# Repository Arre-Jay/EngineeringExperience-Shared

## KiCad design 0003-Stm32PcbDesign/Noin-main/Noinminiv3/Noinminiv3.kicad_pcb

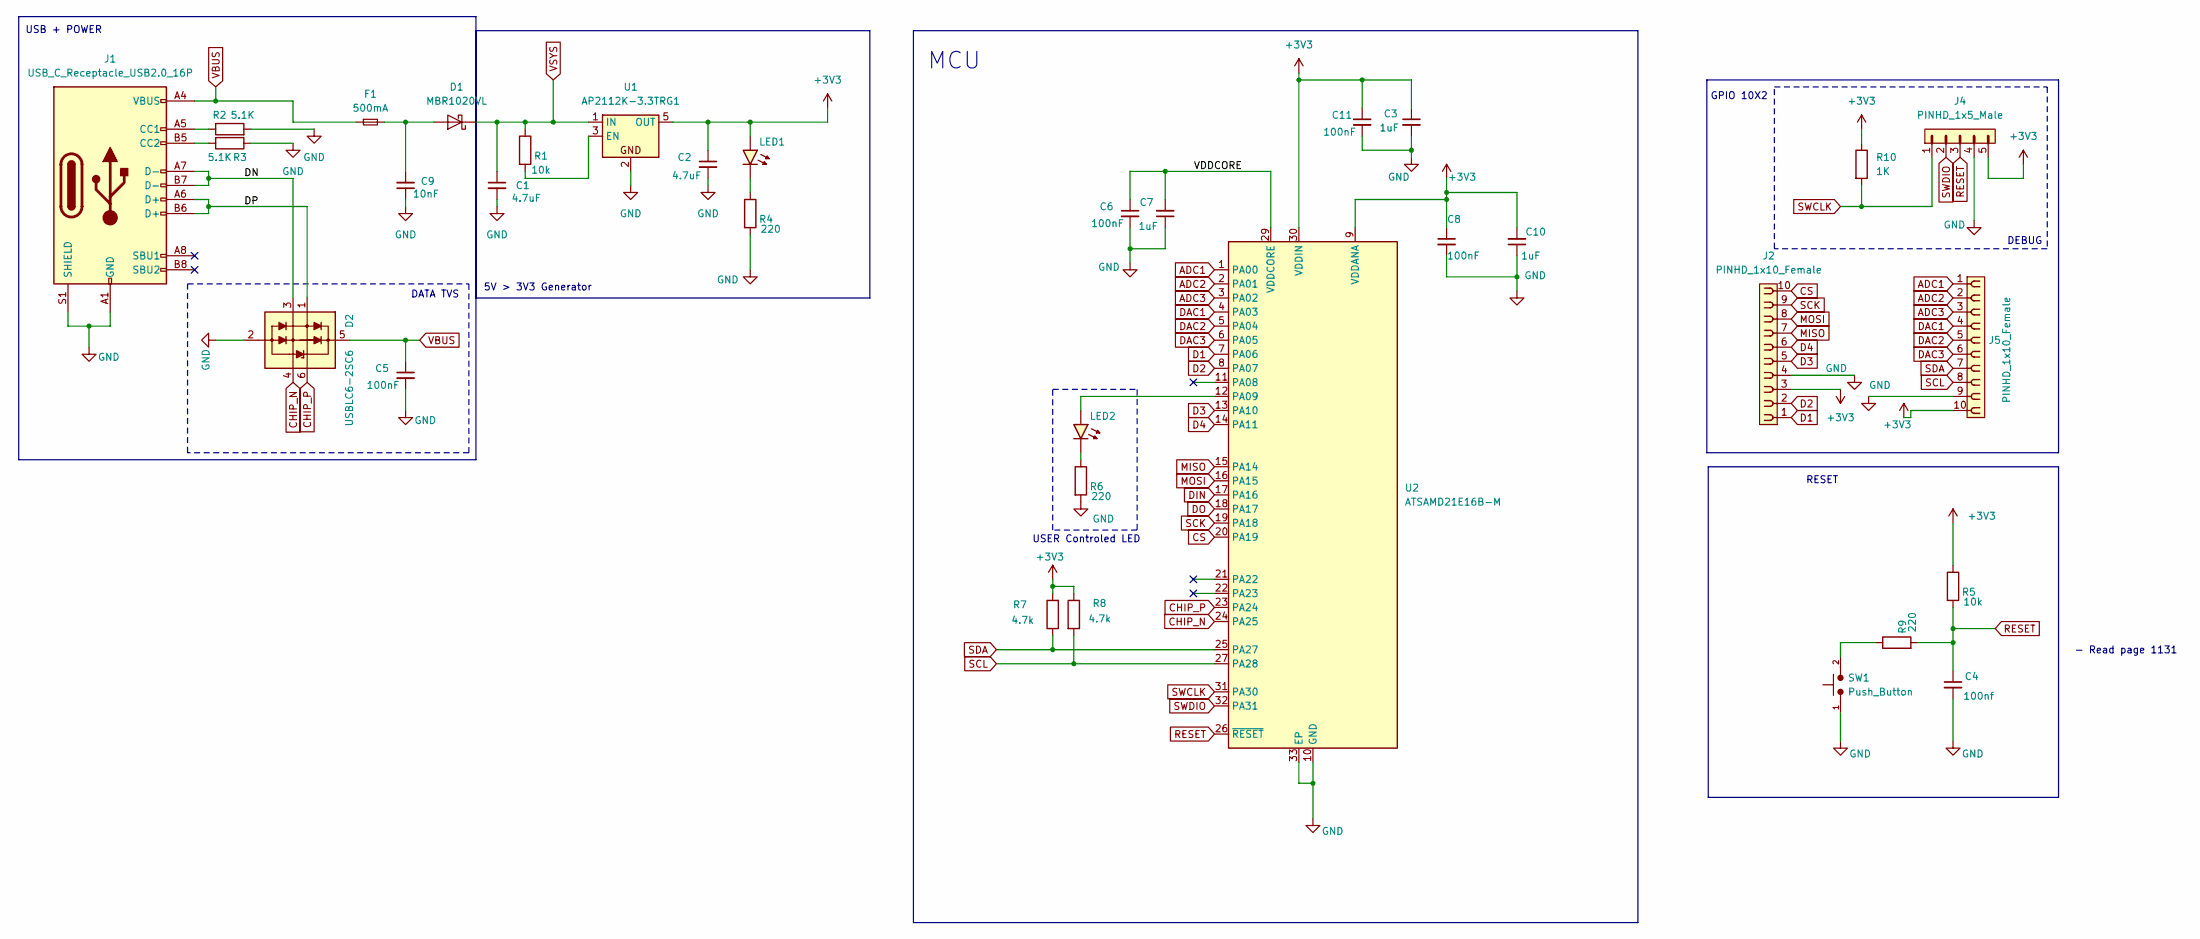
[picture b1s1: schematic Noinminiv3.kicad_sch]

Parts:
C1, C2, C3, C4, C5, C6, C7, C8, C9, C10, C11: 1uF_0603_25V; C_0603_1608Metric; Part Number GRM188R61E105KA12D; JLCPCB ID C15849
D1: MBR1020VL; D_SOD-123F_TVS
D2: USBLC6-2SC6; SOT-23-6
F1: 500mA; Fuse_0603_1608Metric
J1: USB_C_Receptacle_USB2.0_16P; USB_C_Receptacle_HRO_TYPE-C-31-M-12
J2, J5: PINHD_1x10_Female; PinSocket_1x10_P2.54mm_Vertical
J4: PINHD_1x5_Male; PinHeader_1x05_P2.54mm_Vertical
LED1, LED2: LED_1.8mm_SMD_Red; LED_0402_1005Metric
R1, R2, R3, R4, R5, R6, R7, R8, R9: 10k_0402; R_0402; Part Number RT0402FRE0710KL
R10: 1K; R_0402; Manufacturer Part Number 0402WGF1001TCE
SW1: Push_Button; SW_Push_SPST_NO_Alps_SKRK
U1: AP2112K-3.3TRG1; SOT-23-5
U2: ATSAMD21E16B-M; QFN-32-1EP_5x5mm_P0.5mm_EP3.6x3.6mm

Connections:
+3V3: C2.1, C3.1, C8.1, C10.2, C11.1, J2.3, J4.5, J5.10, LED1.2 (A), R5.1, R7.2, R8.1, R10.1, U1.5 (OUT), U2.9 (VDDANA), U2.30 (VDDIN)
/DN: D2.3 (L2), J1.A7 (D-), J1.B7 (D-)
/DP: D2.1 (L1), J1.A6 (D+), J1.B6 (D+)
/VDDCORE: C6.1, C7.2, U2.29 (VDDCORE)
ADC1: J5.1, U2.1 (PA00)
ADC2: J5.2, U2.2 (PA01)
ADC3: J5.3, U2.3 (PA02)
CHIP_N: D2.4 (L2), U2.24 (PA25)
CHIP_P: D2.6 (L1), U2.23 (PA24)
CS: J2.10, U2.20 (PA19)
D1: J2.1, U2.7 (PA06)
D2: J2.2, U2.8 (PA07)
D3: J2.5, U2.13 (PA10)
D4: J2.6, U2.14 (PA11)
DAC1: J5.4, U2.4 (PA03)
DAC2: J5.5, U2.5 (PA04)
DAC3: J5.6, U2.6 (PA05)
DIN: U2.17 (PA16)
DO: U2.18 (PA17)
GND: C1.2, C2.2, C3.2, C4.2, C5.2, C6.2, C7.1, C8.2, C9.1, C10.1, C11.2, D2.2 (VN), J1.A1 (GND), J1.A12 (GND), J1.B1 (GND), J1.B12 (GND), J1.S1 (SHIELD), J2.4, J4.4, J5.9, R2.2, R3.1, R4.2, R6.2, SW1.1, U1.2, U2.10 (GND), U2.28 (GND), U2.33 (EP)
MISO: J2.7, U2.15 (PA14)
MOSI: J2.8, U2.16 (PA15)
unnamed: C9.2, D1.2 (A), F1.2
unnamed: J1.A5 (CC1), R2.1
unnamed: J1.B5 (CC2), R3.2
unnamed: LED1.1 (K), R4.1
unnamed: LED2.2 (A), U2.12 (PA09)
unnamed: LED2.1 (K), R6.1
unnamed: R9.1, SW1.2
unnamed: R1.2, U1.3 (EN)
RESET: C4.1, J4.3, R5.2, R9.2, U2.26 (~RESET)
SCK: J2.9, U2.19 (PA18)
SCL: J5.8, R8.2, U2.27 (PA28)
SDA: J5.7, R7.1, U2.25 (PA27)
SWCLK: J4.1, R10.2, U2.31 (PA30)
SWDIO: J4.2, U2.32 (PA31)
VBUS: C5.1, D2.5 (VP), F1.1, J1.A4 (VBUS), J1.A9 (VBUS), J1.B4 (VBUS), J1.B9 (VBUS)
VSYS: C1.1, D1.1 (K), R1.1, U1.1 (IN)

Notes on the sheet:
- Read page 1131
5V > 3V3 Generator
DATA TVS
DEBUG
GPIO 10X2
USER Controled LED
USB + POWER
RESET
MCU

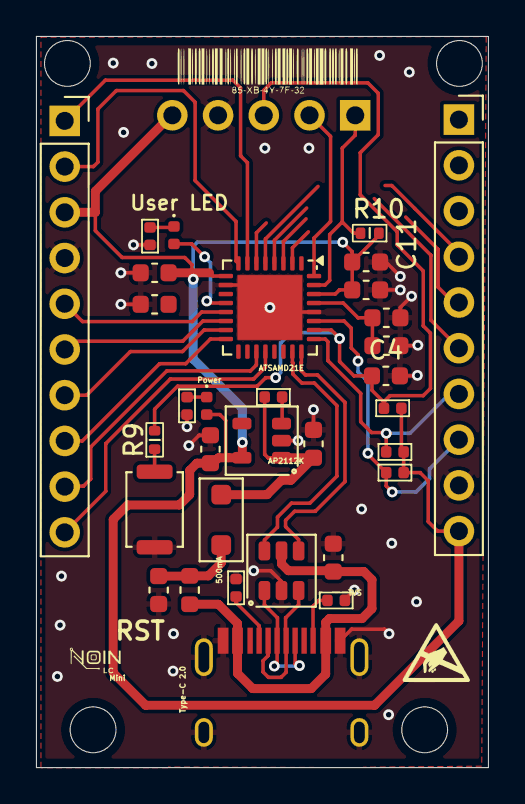
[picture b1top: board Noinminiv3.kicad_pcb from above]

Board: 2 copper layers, 25.1 x 40.6 mm, 33 parts (0 on the bottom side), 36 nets.

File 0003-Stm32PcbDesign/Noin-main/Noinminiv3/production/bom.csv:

Designator,Footprint,Quantity,Value,LCSC Part #
"C1, C10, C2, C3, C4, C5, C6, C7, C8, C9",0603,10,1uF_0603_25V,
D1,D_SOD-123F_TVS,1,MBR1020VL,
D2,SOT-23-6,1,USBLC6-2SC6,
F1,0603,1,500mA,
J1,USB_C_Receptacle_HRO_TYPE-C-31-M-12,1,USB_C_Receptacle_USB2.0_16P,
"J2, J5",PinSocket_1x10_P2.54mm_Vertical,2,PINHD_1x10_Female,
J4,PinHeader_1x05_P2.54mm_Vertical,1,PINHD_1x5_Male,
"LED1, LED2",0402,2,LED_1.8mm_SMD_Red,
"R1, R2, R3, R4, R5, R6, R7, R8",R_0402,8,10k_0402,
SW1,SW_Push_SPST_NO_Alps_SKRK,1,Push_Button,
U1,SOT-23-5,1,AP2112K-3.3TRG1,
U2,QFN-32-1EP_5x5mm_P0.5mm_EP3.6x3.6mm,1,ATSAMD21E16B-M,

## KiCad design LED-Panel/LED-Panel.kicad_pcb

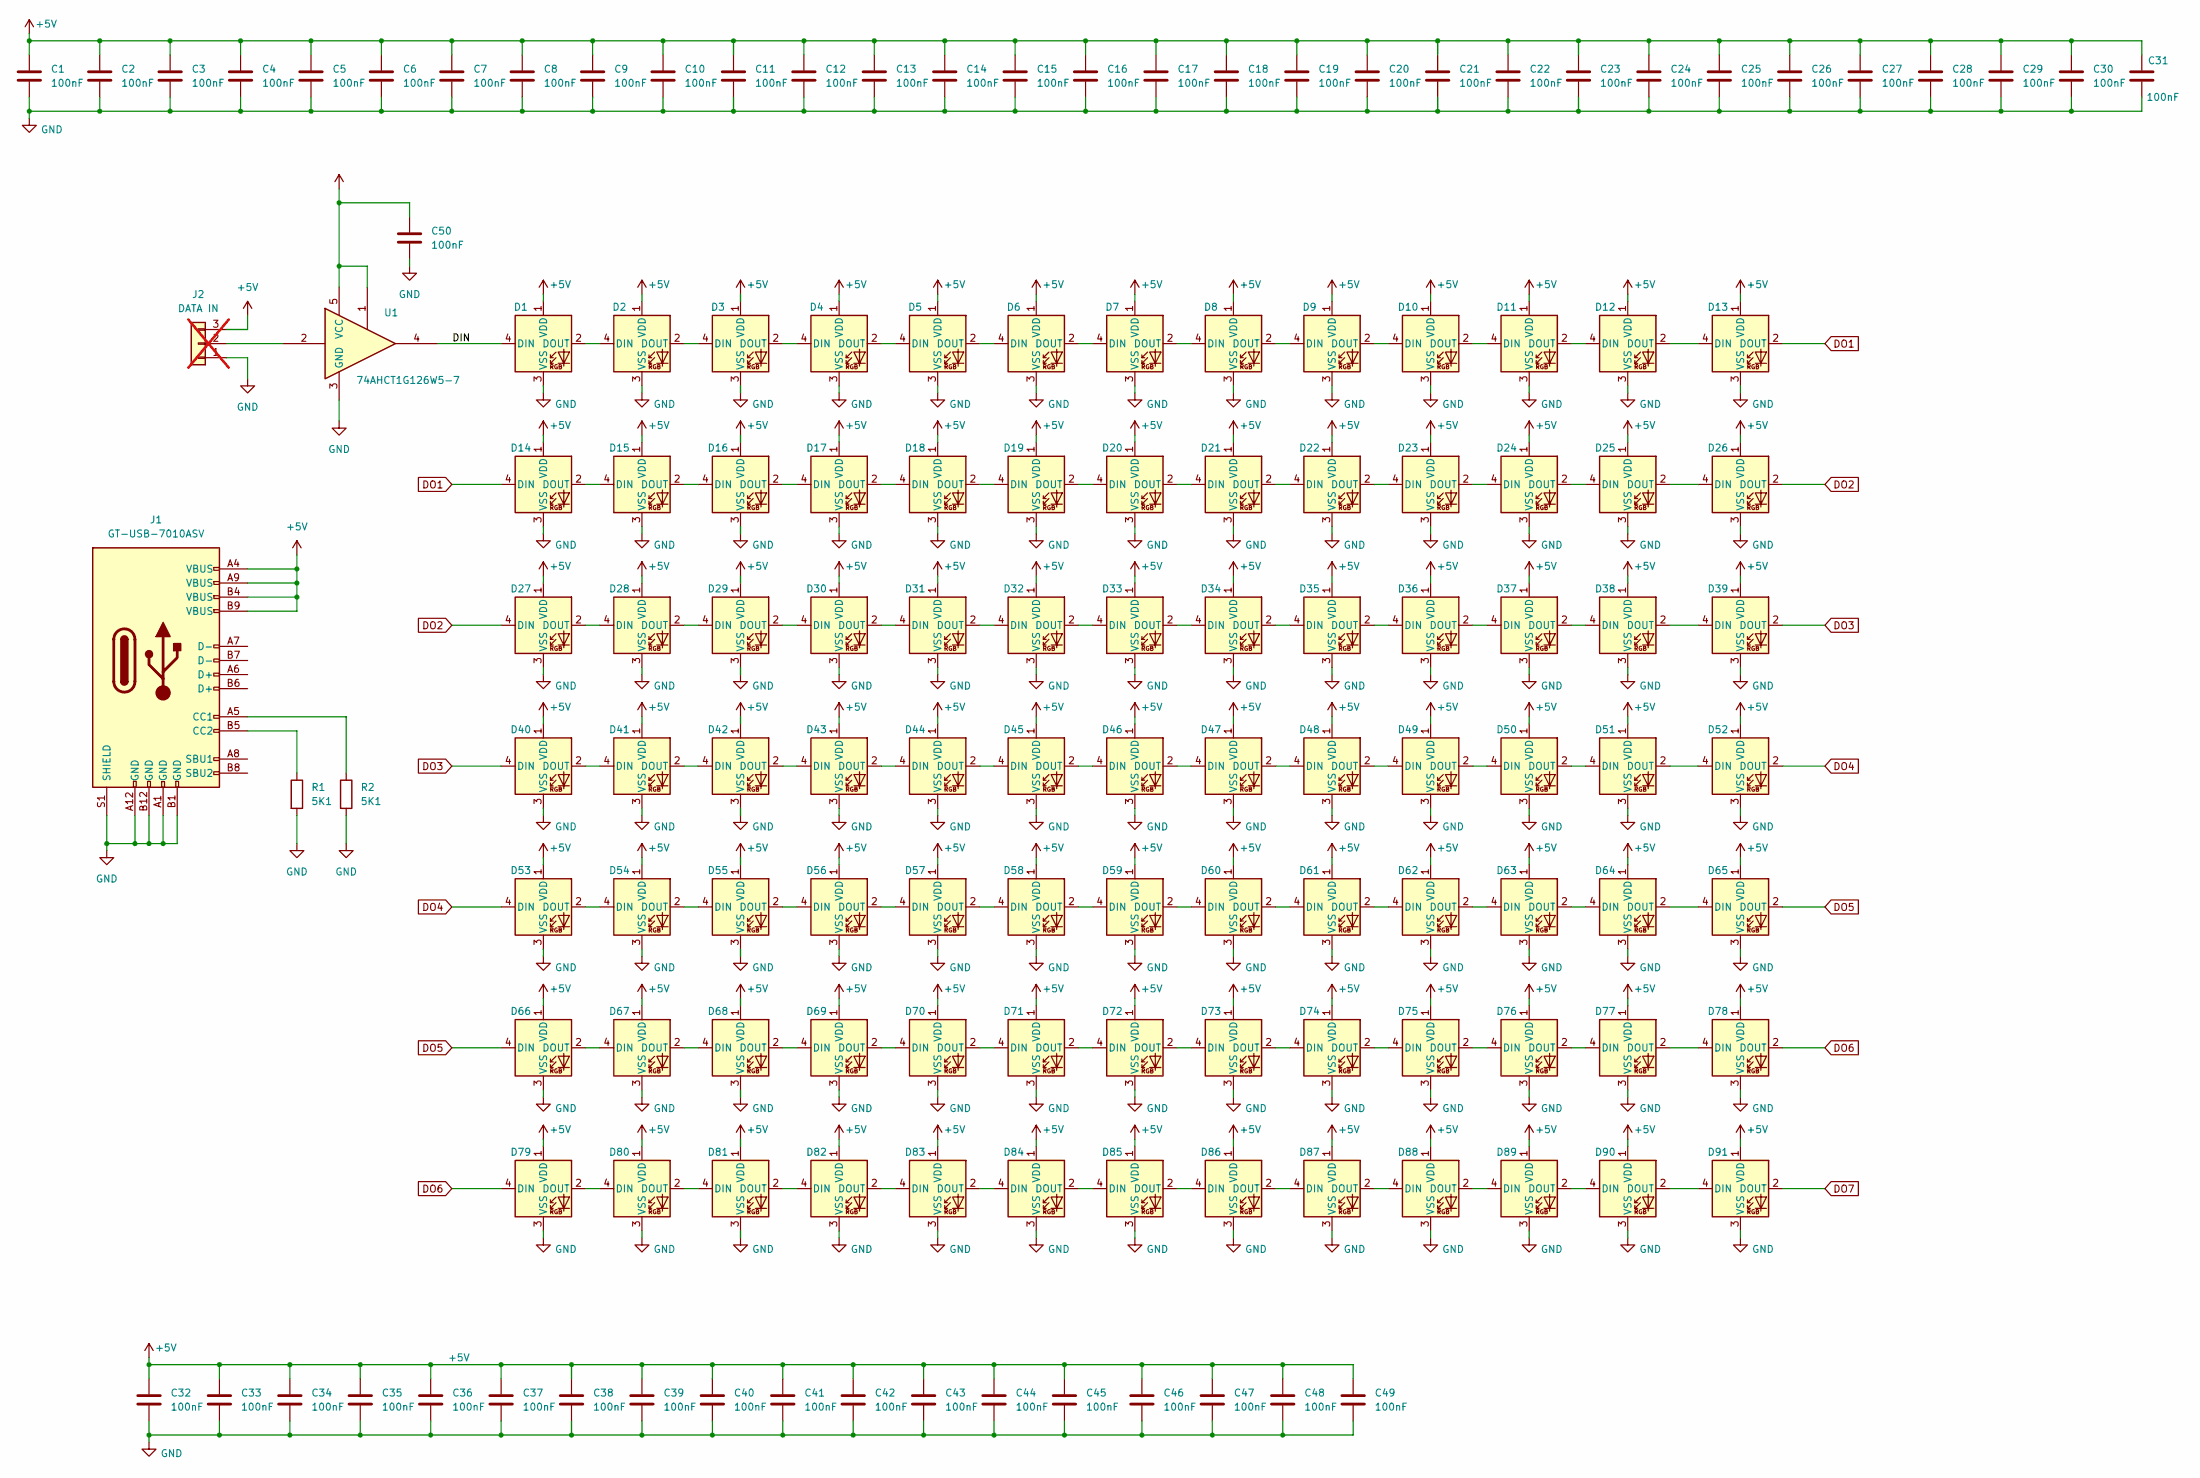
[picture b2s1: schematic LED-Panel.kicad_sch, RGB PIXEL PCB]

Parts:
C1, C2, C3, C4, C5, C6, C7, C8, C9, C10, C11, C12, C13, C14, C15, C16, C17, C18, C19, C20, C21, C22, C23, C24, C25, C26, C27, C28, C29, C30, C31, C32, C33, C34, C35, C36, C37, C38, C39, C40, C41, C42, C43, C44, C45, C46, C47, C48, C49, C50: 100nF; C_0402; Manufacturer Part Number CGA0402X7R104K160GT
D1, D2, D3, D4, D5, D6, D7, D8, D9, D10, D11, D12, D13, D14, D15, D16, D17, D18, D19, D20, D21, D22, D23, D24, D25, D26, D27, D28, D29, D30, D31, D32, D33, D34, D35, D36, D37, D38, D39, D40, D41, D42, D43, D44, D45, D46, D47, D48, D49, D50, D51, D52, D53, D54, D55, D56, D57, D58, D59, D60, D61, D62, D63, D64, D65, D66, D67, D68, D69, D70, D71, D72, D73, D74, D75, D76, D77, D78, D79, D80, D81, D82, D83, D84, D85, D86, D87, D88, D89, D90, D91: XL-5050RGBC-WS2812B; Manufacturer Part Number XL-5050RGBC-WS2812B
J1: GT-USB-7010ASV; G-Switch_GT-USB-7010ASV; Manufacturer Part Number GT-USB-7010ASV
J2: DATA IN; PinSocket_1x03_P2.54mm_Vertical; not fitted
R1, R2: 5K1; R_0402; Manufacturer Part Number RT0402FRE075K1L
U1: 74AHCT1G126W5-7; Manufacturer Part Number 74AHCT1G126W5-7

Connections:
+5V: C1.1, C2.1, C3.1, C4.1, C5.1, C6.1, C7.1, C8.1, C9.1, C10.1, C11.1, C12.1, C13.1, C14.1, C15.1, C16.1, C17.1, C18.1, C19.1, C20.1, C21.1, C22.1, C23.1, C24.1, C25.1, C26.1, C27.1, C28.1, C29.1, C30.1, C31.1, C32.1, C33.1, C34.1, C35.1, C36.1, C37.1, C38.1, C39.1, C40.1, C41.1, C42.1, C43.1, C44.1, C45.1, C46.1, C47.1, C48.1, C49.1, C50.1, D1.1 (VDD), D2.1 (VDD), D3.1 (VDD), D4.1 (VDD), D5.1 (VDD), D6.1 (VDD), D7.1 (VDD), D8.1 (VDD), D9.1 (VDD), D10.1 (VDD), D11.1 (VDD), D12.1 (VDD), D13.1 (VDD), D14.1 (VDD), D15.1 (VDD), D16.1 (VDD), D17.1 (VDD), D18.1 (VDD), D19.1 (VDD), D20.1 (VDD), D21.1 (VDD), D22.1 (VDD), D23.1 (VDD), D24.1 (VDD), D25.1 (VDD), D26.1 (VDD), D27.1 (VDD), D28.1 (VDD), D29.1 (VDD), D30.1 (VDD), D31.1 (VDD), D32.1 (VDD), D33.1 (VDD), D34.1 (VDD), D35.1 (VDD), D36.1 (VDD), D37.1 (VDD), D38.1 (VDD), D39.1 (VDD), D40.1 (VDD), D41.1 (VDD), D42.1 (VDD), D43.1 (VDD), D44.1 (VDD), D45.1 (VDD), D46.1 (VDD), D47.1 (VDD), D48.1 (VDD), D49.1 (VDD), D50.1 (VDD), D51.1 (VDD), D52.1 (VDD), D53.1 (VDD), D54.1 (VDD), D55.1 (VDD), D56.1 (VDD), D57.1 (VDD), D58.1 (VDD), D59.1 (VDD), D60.1 (VDD), D61.1 (VDD), D62.1 (VDD), D63.1 (VDD), D64.1 (VDD), D65.1 (VDD), D66.1 (VDD), D67.1 (VDD), D68.1 (VDD), D69.1 (VDD), D70.1 (VDD), D71.1 (VDD), D72.1 (VDD), D73.1 (VDD), D74.1 (VDD), D75.1 (VDD), D76.1 (VDD), D77.1 (VDD), D78.1 (VDD), D79.1 (VDD), D80.1 (VDD), D81.1 (VDD), D82.1 (VDD), D83.1 (VDD), D84.1 (VDD), D85.1 (VDD), D86.1 (VDD), D87.1 (VDD), D88.1 (VDD), D89.1 (VDD), D90.1 (VDD), D91.1 (VDD), J1.A4 (VBUS), J1.A9 (VBUS), J1.B4 (VBUS), J1.B9 (VBUS), J2.3, U1.1, U1.5 (VCC)
/DIN: D1.4 (DIN), U1.4
DO1: D13.2 (DOUT), D14.4 (DIN)
DO2: D26.2 (DOUT), D27.4 (DIN)
DO3: D39.2 (DOUT), D40.4 (DIN)
DO4: D52.2 (DOUT), D53.4 (DIN)
DO5: D65.2 (DOUT), D66.4 (DIN)
DO6: D78.2 (DOUT), D79.4 (DIN)
DO7: D91.2 (DOUT)
GND: C1.2, C2.2, C3.2, C4.2, C5.2, C6.2, C7.2, C8.2, C9.2, C10.2, C11.2, C12.2, C13.2, C14.2, C15.2, C16.2, C17.2, C18.2, C19.2, C20.2, C21.2, C22.2, C23.2, C24.2, C25.2, C26.2, C27.2, C28.2, C29.2, C30.2, C31.2, C32.2, C33.2, C34.2, C35.2, C36.2, C37.2, C38.2, C39.2, C40.2, C41.2, C42.2, C43.2, C44.2, C45.2, C46.2, C47.2, C48.2, C49.2, C50.2, D1.3 (VSS), D2.3 (VSS), D3.3 (VSS), D4.3 (VSS), D5.3 (VSS), D6.3 (VSS), D7.3 (VSS), D8.3 (VSS), D9.3 (VSS), D10.3 (VSS), D11.3 (VSS), D12.3 (VSS), D13.3 (VSS), D14.3 (VSS), D15.3 (VSS), D16.3 (VSS), D17.3 (VSS), D18.3 (VSS), D19.3 (VSS), D20.3 (VSS), D21.3 (VSS), D22.3 (VSS), D23.3 (VSS), D24.3 (VSS), D25.3 (VSS), D26.3 (VSS), D27.3 (VSS), D28.3 (VSS), D29.3 (VSS), D30.3 (VSS), D31.3 (VSS), D32.3 (VSS), D33.3 (VSS), D34.3 (VSS), D35.3 (VSS), D36.3 (VSS), D37.3 (VSS), D38.3 (VSS), D39.3 (VSS), D40.3 (VSS), D41.3 (VSS), D42.3 (VSS), D43.3 (VSS), D44.3 (VSS), D45.3 (VSS), D46.3 (VSS), D47.3 (VSS), D48.3 (VSS), D49.3 (VSS), D50.3 (VSS), D51.3 (VSS), D52.3 (VSS), D53.3 (VSS), D54.3 (VSS), D55.3 (VSS), D56.3 (VSS), D57.3 (VSS), D58.3 (VSS), D59.3 (VSS), D60.3 (VSS), D61.3 (VSS), D62.3 (VSS), D63.3 (VSS), D64.3 (VSS), D65.3 (VSS), D66.3 (VSS), D67.3 (VSS), D68.3 (VSS), D69.3 (VSS), D70.3 (VSS), D71.3 (VSS), D72.3 (VSS), D73.3 (VSS), D74.3 (VSS), D75.3 (VSS), D76.3 (VSS), D77.3 (VSS), D78.3 (VSS), D79.3 (VSS), D80.3 (VSS), D81.3 (VSS), D82.3 (VSS), D83.3 (VSS), D84.3 (VSS), D85.3 (VSS), D86.3 (VSS), D87.3 (VSS), D88.3 (VSS), D89.3 (VSS), D90.3 (VSS), D91.3 (VSS), J1.A1 (GND), J1.A12 (GND), J1.B1 (GND), J1.B12 (GND), J1.S1 (SHIELD), J2.1, R1.2, R2.2, U1.3 (GND)
unnamed: D1.2 (DOUT), D2.4 (DIN)
unnamed: D2.2 (DOUT), D3.4 (DIN)
unnamed: D3.2 (DOUT), D4.4 (DIN)
unnamed: D4.2 (DOUT), D5.4 (DIN)
unnamed: D5.2 (DOUT), D6.4 (DIN)
unnamed: D6.2 (DOUT), D7.4 (DIN)
unnamed: D7.2 (DOUT), D8.4 (DIN)
unnamed: D8.2 (DOUT), D9.4 (DIN)
unnamed: D9.2 (DOUT), D10.4 (DIN)
unnamed: D10.2 (DOUT), D11.4 (DIN)
unnamed: D11.2 (DOUT), D12.4 (DIN)
unnamed: D12.2 (DOUT), D13.4 (DIN)
unnamed: D14.2 (DOUT), D15.4 (DIN)
unnamed: D15.2 (DOUT), D16.4 (DIN)
unnamed: D16.2 (DOUT), D17.4 (DIN)
unnamed: D17.2 (DOUT), D18.4 (DIN)
unnamed: D18.2 (DOUT), D19.4 (DIN)
unnamed: D19.2 (DOUT), D20.4 (DIN)
unnamed: D20.2 (DOUT), D21.4 (DIN)
unnamed: D21.2 (DOUT), D22.4 (DIN)
unnamed: D22.2 (DOUT), D23.4 (DIN)
unnamed: D23.2 (DOUT), D24.4 (DIN)
unnamed: D24.2 (DOUT), D25.4 (DIN)
unnamed: D25.2 (DOUT), D26.4 (DIN)
unnamed: D27.2 (DOUT), D28.4 (DIN)
unnamed: D28.2 (DOUT), D29.4 (DIN)
unnamed: D29.2 (DOUT), D30.4 (DIN)
unnamed: D30.2 (DOUT), D31.4 (DIN)
unnamed: D31.2 (DOUT), D32.4 (DIN)
unnamed: D32.2 (DOUT), D33.4 (DIN)
unnamed: D33.2 (DOUT), D34.4 (DIN)
unnamed: D34.2 (DOUT), D35.4 (DIN)
unnamed: D35.2 (DOUT), D36.4 (DIN)
unnamed: D36.2 (DOUT), D37.4 (DIN)
unnamed: D37.2 (DOUT), D38.4 (DIN)
unnamed: D38.2 (DOUT), D39.4 (DIN)
unnamed: D40.2 (DOUT), D41.4 (DIN)
unnamed: D41.2 (DOUT), D42.4 (DIN)
unnamed: D42.2 (DOUT), D43.4 (DIN)
unnamed: D43.2 (DOUT), D44.4 (DIN)
unnamed: D44.2 (DOUT), D45.4 (DIN)
unnamed: D45.2 (DOUT), D46.4 (DIN)
unnamed: D46.2 (DOUT), D47.4 (DIN)
unnamed: D47.2 (DOUT), D48.4 (DIN)
unnamed: D48.2 (DOUT), D49.4 (DIN)
unnamed: D49.2 (DOUT), D50.4 (DIN)
unnamed: D50.2 (DOUT), D51.4 (DIN)
unnamed: D51.2 (DOUT), D52.4 (DIN)
unnamed: D53.2 (DOUT), D54.4 (DIN)
unnamed: D54.2 (DOUT), D55.4 (DIN)
unnamed: D55.2 (DOUT), D56.4 (DIN)
unnamed: D56.2 (DOUT), D57.4 (DIN)
unnamed: D57.2 (DOUT), D58.4 (DIN)
unnamed: D58.2 (DOUT), D59.4 (DIN)
unnamed: D59.2 (DOUT), D60.4 (DIN)
unnamed: D60.2 (DOUT), D61.4 (DIN)
unnamed: D61.2 (DOUT), D62.4 (DIN)
unnamed: D62.2 (DOUT), D63.4 (DIN)
unnamed: D63.2 (DOUT), D64.4 (DIN)
unnamed: D64.2 (DOUT), D65.4 (DIN)
unnamed: D66.2 (DOUT), D67.4 (DIN)
unnamed: D67.2 (DOUT), D68.4 (DIN)
unnamed: D68.2 (DOUT), D69.4 (DIN)
unnamed: D69.2 (DOUT), D70.4 (DIN)
unnamed: D70.2 (DOUT), D71.4 (DIN)
unnamed: D71.2 (DOUT), D72.4 (DIN)
unnamed: D72.2 (DOUT), D73.4 (DIN)
unnamed: D73.2 (DOUT), D74.4 (DIN)
unnamed: D74.2 (DOUT), D75.4 (DIN)
unnamed: D75.2 (DOUT), D76.4 (DIN)
unnamed: D76.2 (DOUT), D77.4 (DIN)
unnamed: D77.2 (DOUT), D78.4 (DIN)
unnamed: D79.2 (DOUT), D80.4 (DIN)
unnamed: D80.2 (DOUT), D81.4 (DIN)
unnamed: D81.2 (DOUT), D82.4 (DIN)
unnamed: D82.2 (DOUT), D83.4 (DIN)
unnamed: D83.2 (DOUT), D84.4 (DIN)
unnamed: D84.2 (DOUT), D85.4 (DIN)
unnamed: D85.2 (DOUT), D86.4 (DIN)
unnamed: D86.2 (DOUT), D87.4 (DIN)
unnamed: D87.2 (DOUT), D88.4 (DIN)
unnamed: D88.2 (DOUT), D89.4 (DIN)
unnamed: D89.2 (DOUT), D90.4 (DIN)
unnamed: D90.2 (DOUT), D91.4 (DIN)
unnamed: J1.A5 (CC1), R2.1
unnamed: J1.B5 (CC2), R1.1
unnamed: J2.2, U1.2

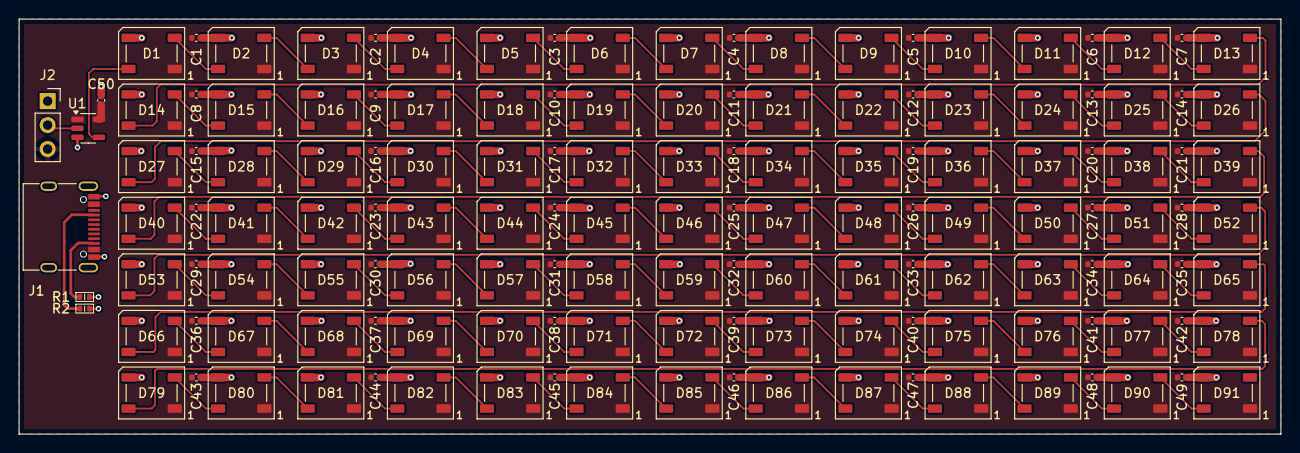
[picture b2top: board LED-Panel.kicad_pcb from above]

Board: 2 copper layers, 133.8 x 44.0 mm, 146 parts (0 on the bottom side), 96 nets.

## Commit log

2025-04-21 Added LED Panel Project
2025-05-06 Added Plant-Code
2025-09-30 reddit-circuit change added
2025-09-30 added library
2025-09-30 updated refernce
